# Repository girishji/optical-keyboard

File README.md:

Keyboard PCB for Gateron optical switches (KiCad project).

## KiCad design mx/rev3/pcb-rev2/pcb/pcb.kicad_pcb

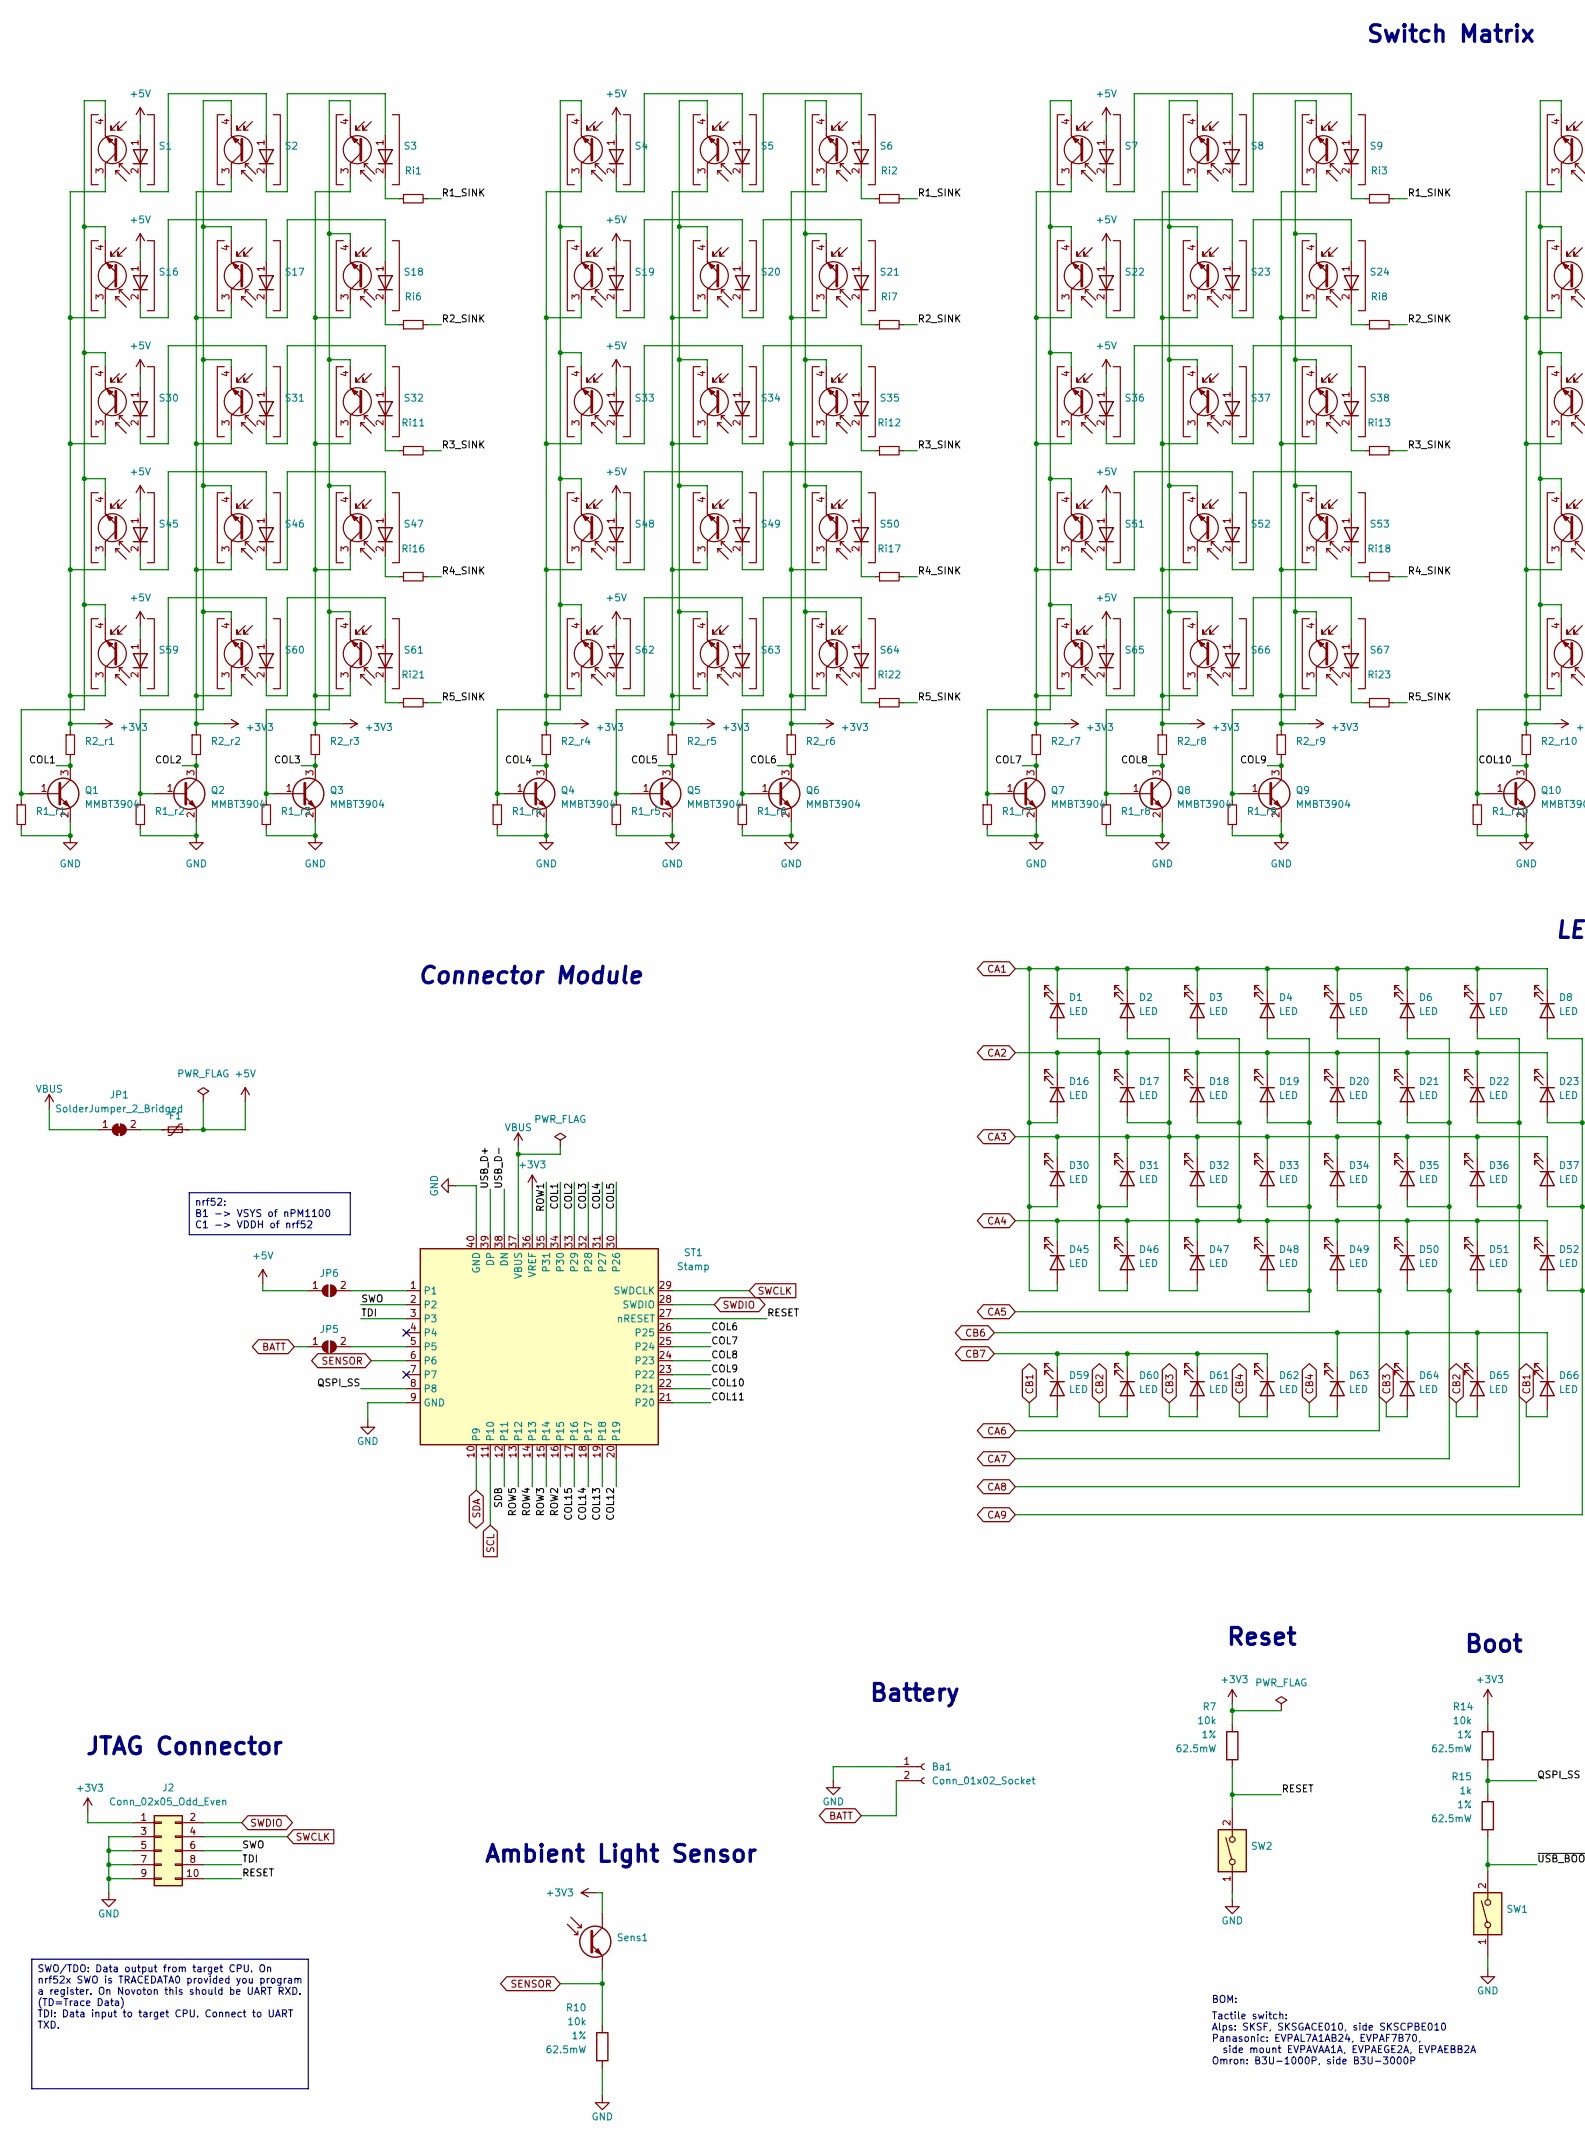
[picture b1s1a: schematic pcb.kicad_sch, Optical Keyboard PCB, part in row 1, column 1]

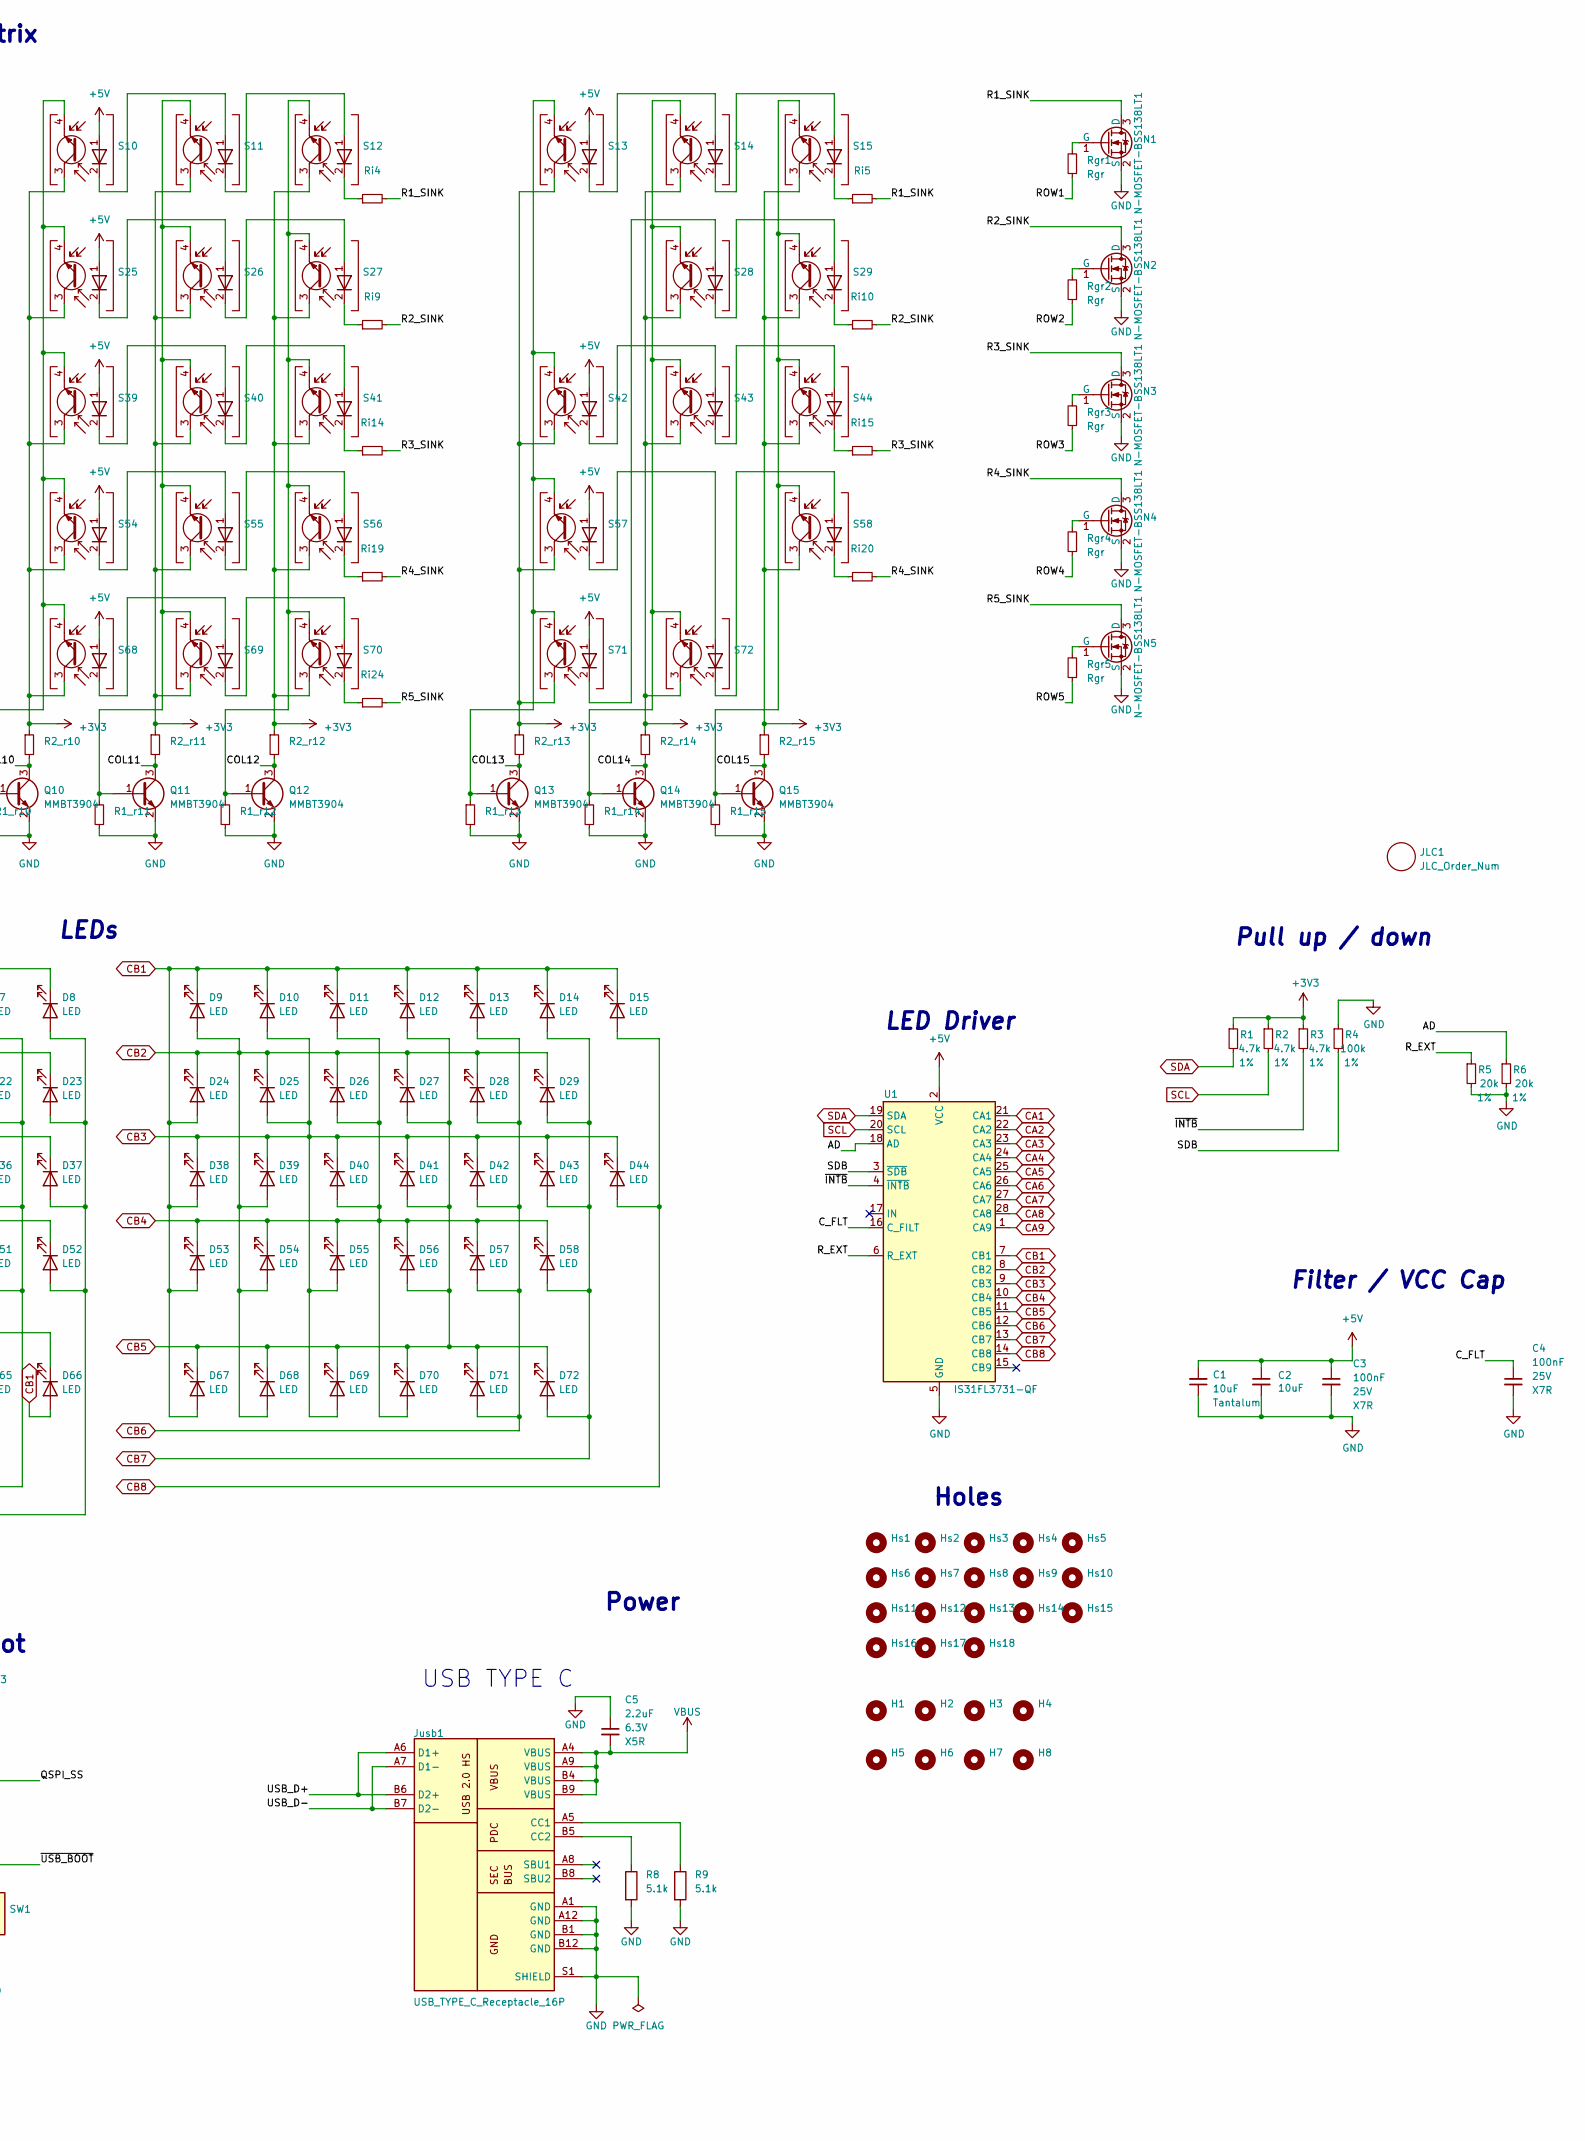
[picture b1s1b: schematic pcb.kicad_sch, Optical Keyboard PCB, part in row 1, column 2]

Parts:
Ba1: Conn_01x02_Socket; Battery_Pads_2x2.0x2.0mm
C1: 10uF; C_1206_3216Metric; JLC 10uF_tantalum
C2: 10uF; C_0603_1608Metric_Pad1.08x0.95mm_HandSolder; MPN CC0603MRX5R8BB106; LCSC C596327
C3, C4: 100nF; C_0603_1608Metric_Pad1.08x0.95mm_HandSolder; VOLTAGE RATING 25V; TOLERANCE TBD; MPN CL05B104KA5NNNC; LCSC C155422
C5: 2.2uF; C_0603_1608Metric_Pad1.08x0.95mm_HandSolder; VOLTAGE RATING 6.3V; TOLERANCE TBD; MPN CL05A225MQ5NNNC; LCSC C107371
D1, D2, D3, D4, D5, D6, D7, D8, D9, D10, D11, D12, D13, D14, D15, D16, D17, D18, D19, D20, D21, D22, D23, D24, D25, D26, D27, D28, D29, D30, D31, D32, D33, D34, D35, D36, D37, D38, D39, D40, D41, D42, D43, D44, D45, D46, D47, D48, D49, D50, D51, D52, D53, D54, D55, D56, D57, D58, D59, D60, D61, D62, D63, D64, D65, D66, D67, D68, D69, D70, D71, D72: LED; LED_0603_1608Metric
F1: 500ma; Fuse_0603_1608Metric; LCSC C210357
H1, H2, H3, H4, H5, H6, H7, H8: MountingHole; SMTSO_M2
Hs1, Hs2, Hs3, Hs4, Hs5, Hs6, Hs7, Hs8, Hs9, Hs10, Hs11, Hs12, Hs13, Hs14, Hs15, Hs16, Hs17, Hs18: SMTSO_M2
J2: Conn_02x05_Odd_Even; PinHeader_2x05_P1.27mm_Horizontal
JLC1: JLC_Order_Num
JP1: SolderJumper_2_Bridged; SolderJumper-2_P1.3mm_Bridged2Bar_RoundedPad1.0x1.5mm
JP5, JP6: SolderJumper_2_Open; SolderJumper-2_P1.3mm_Open_TrianglePad1.0x1.5mm
Jusb1: USB_TYPE_C_Receptacle_16P; USB_C_Receptacle_XKB_U262-16XN-4BVC11; MPN U262-161N-4BVC11; LCSC C319148
N1, N2, N3, N4, N5: N-MOSFET-BSS138LT1; SOT-23-3
Q1, Q2, Q3, Q4, Q5, Q6, Q7, Q8, Q9, Q10, Q11, Q12, Q13, Q14, Q15: MMBT3904; SOT-23
R1, R2, R3: 4.7k; R_0603_1608Metric_Pad0.98x0.95mm_HandSolder; Tolerance 1%; LCSC C105871
R1_r1, R1_r2, R1_r3, R1_r4, R1_r5, R1_r6, R1_r7, R1_r8, R1_r9, R1_r10, R1_r11, R1_r12, R1_r13, R1_r14, R1_r15: R1_r; R_0603_1608Metric; Power Rating 62.5mW; MPN RC0402FR-07160RL; LCSC C327369
R2_r1, R2_r2, R2_r3, R2_r4, R2_r5, R2_r6, R2_r7, R2_r8, R2_r9, R2_r10, R2_r11, R2_r12, R2_r13, R2_r14, R2_r15: R2_r; R_0603_1608Metric; Power Rating 62.5mW; MPN RC0402FR-07160RL; LCSC C327369
R4: 100k; R_0603_1608Metric_Pad0.98x0.95mm_HandSolder; Tolerance 1%; JLC 20k
R5, R6: 20k; R_0603_1608Metric_Pad0.98x0.95mm_HandSolder; Tolerance 1%; JLC 20k
R7, R10, R14: 10k; R_0603_1608Metric_Pad0.98x0.95mm_HandSolder; TOLERANCE 1%; POWER RATING 62.5mW; MPN RC0402FR-0710KL; LCSC C60490
R8, R9: 5.1k; R_0603_1608Metric_Pad0.98x0.95mm_HandSolder; TOLERANCE 1%; POWER RATING 62.5mW; MPN RC0402FR-075K1L; LCSC C105872
R15: 1k; R_0603_1608Metric_Pad0.98x0.95mm_HandSolder; TOLERANCE 1%; POWER RATING 62.5mW; MPN RC0402FR-071KL; LCSC C106235
Rgr1, Rgr2, Rgr3, Rgr4, Rgr5: Rgr; R_0603_1608Metric; Power Rating 62.5mW; MPN RC0402FR-07160RL; LCSC C327369
Ri1, Ri2, Ri3, Ri4, Ri5, Ri6, Ri7, Ri8, Ri9, Ri10, Ri11, Ri12, Ri13, Ri14, Ri15, Ri16, Ri17, Ri18, Ri19, Ri20, Ri21, Ri22, Ri23, Ri24: R_IR; R_0603_1608Metric
S1, S2, S3, S4, S5, S6, S7, S8, S9, S10, S11, S12, S13, S14, S15, S16, S17, S18, S19, S20, S21, S22, S23, S24, S25, S26, S27, S28, S29, S30, S31, S32, S33, S34, S35, S36, S37, S38, S39, S40, S41, S42, S43, S44, S45, S46, S47, S48, S49, S50, S51, S52, S53, S54, S55, S56, S57, S58, S59, S60, S61, S62, S65, S67, S68, S69, S70, S71, S72: OSw; Gateron_1u_v2
S63: OSw; Gateron_1.25u_v2
S64, S66: OSw; Gateron_2u_v2
ST1: Stamp; StampConnector
SW1, SW2: SW_DIP_x01_XKB_TS_2030; SW_B3U-3000P; MPN TS-2030-B; LCSC C2960614
Sens1: ALS-PT19; MPN 1N4148WT T4; LCSC C68948
U1: IS31FL3731-QF; QFN-28-1EP_4x4mm_P0.4mm_EP2.3x2.3mm; JLCPCB IS31FL3731-QFLS2-TR

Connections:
+3V3: J2.1, R1.1, R2.1, R2_r1.1, R2_r2.1, R2_r3.1, R2_r4.1, R2_r5.1, R2_r6.1, R2_r7.1, R2_r8.1, R2_r9.1, R2_r10.1, R2_r11.1, R2_r12.1, R2_r13.1, R2_r14.1, R2_r15.1, R3.1, R7.1, R14.1, S1.3 (C), S2.3 (C), S3.3 (C), S4.3 (C), S5.3 (C), S6.3 (C), S7.3 (C), S8.3 (C), S9.3 (C), S10.3 (C), S11.3 (C), S12.3 (C), S13.3 (C), S14.3 (C), S15.3 (C), S16.3 (C), S17.3 (C), S18.3 (C), S19.3 (C), S20.3 (C), S21.3 (C), S22.3 (C), S23.3 (C), S24.3 (C), S25.3 (C), S26.3 (C), S27.3 (C), S28.3 (C), S29.3 (C), S30.3 (C), S31.3 (C), S32.3 (C), S33.3 (C), S34.3 (C), S35.3 (C), S36.3 (C), S37.3 (C), S38.3 (C), S39.3 (C), S40.3 (C), S41.3 (C), S42.3 (C), S43.3 (C), S44.3 (C), S45.3 (C), S46.3 (C), S47.3 (C), S48.3 (C), S49.3 (C), S50.3 (C), S51.3 (C), S52.3 (C), S53.3 (C), S54.3 (C), S55.3 (C), S56.3 (C), S57.3 (C), S58.3 (C), S59.3 (C), S60.3 (C), S61.3 (C), S62.3 (C), S63.3 (C), S64.3 (C), S65.3 (C), S66.3 (C), S67.3 (C), S68.3 (C), S69.3 (C), S70.3 (C), S71.3 (C), S72.3 (C), ST1.36 (VREF), Sens1.1 (C)
+5V: C1.2, C2.1, C3.1, F1.2, JP6.1 (A), S1.1 (IR_A), S4.1 (IR_A), S7.1 (IR_A), S10.1 (IR_A), S13.1 (IR_A), S16.1 (IR_A), S19.1 (IR_A), S22.1 (IR_A), S25.1 (IR_A), S30.1 (IR_A), S33.1 (IR_A), S36.1 (IR_A), S39.1 (IR_A), S42.1 (IR_A), S45.1 (IR_A), S48.1 (IR_A), S51.1 (IR_A), S54.1 (IR_A), S57.1 (IR_A), S59.1 (IR_A), S62.1 (IR_A), S65.1 (IR_A), S68.1 (IR_A), S71.1 (IR_A), U1.2 (VCC)
/AD: R6.1, U1.18 (AD)
/COL1: Q1.3 (C), R2_r1.2, ST1.34 (P30)
/COL2: Q2.3 (C), R2_r2.2, ST1.33 (P29)
/COL3: Q3.3 (C), R2_r3.2, ST1.32 (P28)
/COL4: Q4.3 (C), R2_r4.2, ST1.31 (P27)
/COL5: Q5.3 (C), R2_r5.2, ST1.30 (P26)
/COL6: Q6.3 (C), R2_r6.2, ST1.26 (P25)
/COL7: Q7.3 (C), R2_r7.2, ST1.25 (P24)
/COL8: Q8.3 (C), R2_r8.2, ST1.24 (P23)
/COL9: Q9.3 (C), R2_r9.2, ST1.23 (P22)
/COL10: Q10.3 (C), R2_r10.2, ST1.22 (P21)
/COL11: Q11.3 (C), R2_r11.2, ST1.21 (P20)
/COL12: Q12.3 (C), R2_r12.2, ST1.20 (P19)
/COL13: Q13.3 (C), R2_r13.2, ST1.19 (P18)
/COL14: Q14.3 (C), R2_r14.2, ST1.18 (P17)
/COL15: Q15.3 (C), R2_r15.2, ST1.17 (P16)
/C_FLT: C4.1, U1.16 (C_FILT)
/QSPI_SS: R14.2, R15.1, ST1.8
/R1_SINK: N1.3 (D), Ri1.2, Ri2.2, Ri3.2, Ri4.2, Ri5.2
/R2_SINK: N2.3 (D), Ri6.2, Ri7.2, Ri8.2, Ri9.2, Ri10.2
/R3_SINK: N3.3 (D), Ri11.2, Ri12.2, Ri13.2, Ri14.2, Ri15.2
/R4_SINK: N4.3 (D), Ri16.2, Ri17.2, Ri18.2, Ri19.2, Ri20.2
/R5_SINK: N5.3 (D), Ri21.2, Ri22.2, Ri23.2, Ri24.2
/RESET: J2.10, R7.2, ST1.27 (nRESET), SW2.2
/ROW1: Rgr1.1, ST1.35 (P31)
/ROW2: Rgr2.1, ST1.16 (P15)
/ROW3: Rgr3.1, ST1.15 (P14)
/ROW4: Rgr4.1, ST1.14 (P13)
/ROW5: Rgr5.1, ST1.13 (P12)
/R_EXT: R5.1, U1.6 (R_EXT)
/SDB: R4.2, ST1.12 (P11), U1.3 (~SDB)
/SWO: J2.6, ST1.2
/TDI: J2.8, ST1.3
/USB_D+: Jusb1.A6 (D1+), Jusb1.B6 (D2+), ST1.39 (DP)
/USB_D-: Jusb1.A7 (D1-), Jusb1.B7 (D2-), ST1.38 (DN)
/~INTB: R3.2, U1.4 (~INTB)
/~USB_BOOT: R15.2, SW1.2
BATT: Ba1.2, JP5.1 (A)
CA1: D1.1 (K), D2.1 (K), D3.1 (K), D4.1 (K), D5.1 (K), D6.1 (K), D7.1 (K), D8.1 (K), D16.2 (A), D30.2 (A), D45.2 (A), U1.21 (CA1)
CA2: D1.2 (A), D16.1 (K), D17.1 (K), D18.1 (K), D19.1 (K), D20.1 (K), D21.1 (K), D22.1 (K), D23.1 (K), D31.2 (A), D46.2 (A), U1.22 (CA2)
CA3: D2.2 (A), D17.2 (A), D30.1 (K), D31.1 (K), D32.1 (K), D33.1 (K), D34.1 (K), D35.1 (K), D36.1 (K), D37.1 (K), D47.2 (A), U1.23 (CA3)
CA4: D3.2 (A), D18.2 (A), D32.2 (A), D45.1 (K), D46.1 (K), D47.1 (K), D48.1 (K), D49.1 (K), D50.1 (K), D51.1 (K), D52.1 (K), U1.24 (CA4)
CA5: D4.2 (A), D19.2 (A), D33.2 (A), D48.2 (A), U1.25 (CA5)
CA6: D5.2 (A), D20.2 (A), D34.2 (A), D49.2 (A), U1.26 (CA6)
CA7: D6.2 (A), D21.2 (A), D35.2 (A), D50.2 (A), U1.27 (CA7)
CA8: D7.2 (A), D22.2 (A), D36.2 (A), D51.2 (A), U1.28 (CA8)
CA9: D8.2 (A), D23.2 (A), D37.2 (A), D52.2 (A), U1.1 (CA9)
CB1: D9.1 (K), D10.1 (K), D11.1 (K), D12.1 (K), D13.1 (K), D14.1 (K), D15.1 (K), D24.2 (A), D38.2 (A), D53.2 (A), D59.2 (A), D66.2 (A), D67.2 (A), U1.7 (CB1)
CB2: D9.2 (A), D24.1 (K), D25.1 (K), D26.1 (K), D27.1 (K), D28.1 (K), D29.1 (K), D39.2 (A), D54.2 (A), D60.2 (A), D65.2 (A), D68.2 (A), U1.8 (CB2)
CB3: D10.2 (A), D25.2 (A), D38.1 (K), D39.1 (K), D40.1 (K), D41.1 (K), D42.1 (K), D43.1 (K), D44.1 (K), D55.2 (A), D61.2 (A), D64.2 (A), D69.2 (A), U1.9 (CB3)
CB4: D11.2 (A), D26.2 (A), D40.2 (A), D53.1 (K), D54.1 (K), D55.1 (K), D56.1 (K), D57.1 (K), D58.1 (K), D62.2 (A), D63.2 (A), D70.2 (A), U1.10 (CB4)
CB5: D12.2 (A), D27.2 (A), D41.2 (A), D56.2 (A), D67.1 (K), D68.1 (K), D69.1 (K), D70.1 (K), D71.1 (K), D72.1 (K), U1.11 (CB5)
CB6: D13.2 (A), D28.2 (A), D42.2 (A), D57.2 (A), D63.1 (K), D64.1 (K), D65.1 (K), D66.1 (K), D71.2 (A), U1.12 (CB6)
CB7: D14.2 (A), D29.2 (A), D43.2 (A), D58.2 (A), D59.1 (K), D60.1 (K), D61.1 (K), D62.1 (K), D72.2 (A), U1.13 (CB7)
CB8: D15.2 (A), D44.2 (A), U1.14 (CB8)
GND: Ba1.1, C1.1, C2.2, C3.2, C4.2, C5.1, J2.3, J2.5, J2.7, J2.9, Jusb1.A1 (GND), Jusb1.A12 (GND), Jusb1.B1 (GND), Jusb1.B12 (GND), Jusb1.S1 (SHIELD), N1.2 (S), N2.2 (S), N3.2 (S), N4.2 (S), N5.2 (S), Q1.2 (E), Q2.2 (E), Q3.2 (E), Q4.2 (E), Q5.2 (E), Q6.2 (E), Q7.2 (E), Q8.2 (E), Q9.2 (E), Q10.2 (E), Q11.2 (E), Q12.2 (E), Q13.2 (E), Q14.2 (E), Q15.2 (E), R1_r1.2, R1_r2.2, R1_r3.2, R1_r4.2, R1_r5.2, R1_r6.2, R1_r7.2, R1_r8.2, R1_r9.2, R1_r10.2, R1_r11.2, R1_r12.2, R1_r13.2, R1_r14.2, R1_r15.2, R4.1, R5.2, R6.2, R8.2, R9.2, R10.2, ST1.9 (GND), ST1.40 (GND), SW1.1, SW2.1, U1.5 (GND), U1.29 (GND)
unnamed: F1.1, JP1.2 (B)
unnamed: JP5.2 (B), ST1.5
unnamed: JP6.2 (B), ST1.1
unnamed: Jusb1.A5 (CC1), R9.1
unnamed: Jusb1.B5 (CC2), R8.1
unnamed: N1.1 (G), Rgr1.2
unnamed: N2.1 (G), Rgr2.2
unnamed: N3.1 (G), Rgr3.2
unnamed: N4.1 (G), Rgr4.2
unnamed: N5.1 (G), Rgr5.2
unnamed: Q1.1 (B), R1_r1.1, S1.4 (E), S16.4 (E), S30.4 (E), S45.4 (E), S59.4 (E)
unnamed: Q2.1 (B), R1_r2.1, S2.4 (E), S17.4 (E), S31.4 (E), S46.4 (E), S60.4 (E)
unnamed: Q3.1 (B), R1_r3.1, S3.4 (E), S18.4 (E), S32.4 (E), S47.4 (E), S61.4 (E)
unnamed: Q4.1 (B), R1_r4.1, S4.4 (E), S19.4 (E), S33.4 (E), S48.4 (E), S62.4 (E)
unnamed: Q5.1 (B), R1_r5.1, S5.4 (E), S20.4 (E), S34.4 (E), S49.4 (E), S63.4 (E)
unnamed: Q6.1 (B), R1_r6.1, S6.4 (E), S21.4 (E), S35.4 (E), S50.4 (E), S64.4 (E)
unnamed: Q7.1 (B), R1_r7.1, S7.4 (E), S22.4 (E), S36.4 (E), S51.4 (E), S65.4 (E)
unnamed: Q8.1 (B), R1_r8.1, S8.4 (E), S23.4 (E), S37.4 (E), S52.4 (E), S66.4 (E)
unnamed: Q9.1 (B), R1_r9.1, S9.4 (E), S24.4 (E), S38.4 (E), S53.4 (E), S67.4 (E)
unnamed: Q10.1 (B), R1_r10.1, S10.4 (E), S25.4 (E), S39.4 (E), S54.4 (E), S68.4 (E)
unnamed: Q11.1 (B), R1_r11.1, S11.4 (E), S26.4 (E), S40.4 (E), S55.4 (E), S69.4 (E)
unnamed: Q12.1 (B), R1_r12.1, S12.4 (E), S27.4 (E), S41.4 (E), S56.4 (E), S70.4 (E)
unnamed: Q13.1 (B), R1_r13.1, S13.4 (E), S42.4 (E), S57.4 (E), S71.4 (E)
unnamed: Q14.1 (B), R1_r14.1, S14.4 (E), S28.4 (E), S43.4 (E), S72.4 (E)
unnamed: Q15.1 (B), R1_r15.1, S15.4 (E), S29.4 (E), S44.4 (E), S58.4 (E)
unnamed: S1.2 (IR_K), S2.1 (IR_A)
unnamed: S2.2 (IR_K), S3.1 (IR_A)
unnamed: Ri1.1, S3.2 (IR_K)
unnamed: S4.2 (IR_K), S5.1 (IR_A)
unnamed: S5.2 (IR_K), S6.1 (IR_A)
unnamed: Ri2.1, S6.2 (IR_K)
unnamed: S7.2 (IR_K), S8.1 (IR_A)
unnamed: S8.2 (IR_K), S9.1 (IR_A)
unnamed: Ri3.1, S9.2 (IR_K)
unnamed: S10.2 (IR_K), S11.1 (IR_A)
unnamed: S11.2 (IR_K), S12.1 (IR_A)
unnamed: Ri4.1, S12.2 (IR_K)
unnamed: S13.2 (IR_K), S14.1 (IR_A)
unnamed: S14.2 (IR_K), S15.1 (IR_A)
unnamed: Ri5.1, S15.2 (IR_K)
unnamed: S16.2 (IR_K), S17.1 (IR_A)
unnamed: S17.2 (IR_K), S18.1 (IR_A)
unnamed: Ri6.1, S18.2 (IR_K)
unnamed: S19.2 (IR_K), S20.1 (IR_A)
unnamed: S20.2 (IR_K), S21.1 (IR_A)
unnamed: Ri7.1, S21.2 (IR_K)
unnamed: S22.2 (IR_K), S23.1 (IR_A)
unnamed: S23.2 (IR_K), S24.1 (IR_A)
unnamed: Ri8.1, S24.2 (IR_K)
unnamed: S25.2 (IR_K), S26.1 (IR_A)
unnamed: S26.2 (IR_K), S27.1 (IR_A)
unnamed: Ri9.1, S27.2 (IR_K)
unnamed: S28.1 (IR_A), S71.2 (IR_K)
unnamed: S28.2 (IR_K), S29.1 (IR_A)
unnamed: Ri10.1, S29.2 (IR_K)
unnamed: S30.2 (IR_K), S31.1 (IR_A)
unnamed: S31.2 (IR_K), S32.1 (IR_A)
unnamed: Ri11.1, S32.2 (IR_K)
unnamed: S33.2 (IR_K), S34.1 (IR_A)
unnamed: S34.2 (IR_K), S35.1 (IR_A)
unnamed: Ri12.1, S35.2 (IR_K)
unnamed: S36.2 (IR_K), S37.1 (IR_A)
unnamed: S37.2 (IR_K), S38.1 (IR_A)
unnamed: Ri13.1, S38.2 (IR_K)
unnamed: S39.2 (IR_K), S40.1 (IR_A)
unnamed: S40.2 (IR_K), S41.1 (IR_A)
unnamed: Ri14.1, S41.2 (IR_K)
unnamed: S42.2 (IR_K), S43.1 (IR_A)
unnamed: S43.2 (IR_K), S44.1 (IR_A)
unnamed: Ri15.1, S44.2 (IR_K)
unnamed: S45.2 (IR_K), S46.1 (IR_A)
unnamed: S46.2 (IR_K), S47.1 (IR_A)
unnamed: Ri16.1, S47.2 (IR_K)
unnamed: S48.2 (IR_K), S49.1 (IR_A)
unnamed: S49.2 (IR_K), S50.1 (IR_A)
unnamed: Ri17.1, S50.2 (IR_K)
unnamed: S51.2 (IR_K), S52.1 (IR_A)
unnamed: S52.2 (IR_K), S53.1 (IR_A)
unnamed: Ri18.1, S53.2 (IR_K)
unnamed: S54.2 (IR_K), S55.1 (IR_A)
unnamed: S55.2 (IR_K), S56.1 (IR_A)
unnamed: Ri19.1, S56.2 (IR_K)
unnamed: S57.2 (IR_K), S72.1 (IR_A)
unnamed: S58.1 (IR_A), S72.2 (IR_K)
unnamed: Ri20.1, S58.2 (IR_K)
unnamed: S59.2 (IR_K), S60.1 (IR_A)
unnamed: S60.2 (IR_K), S61.1 (IR_A)
unnamed: Ri21.1, S61.2 (IR_K)
unnamed: S62.2 (IR_K), S63.1 (IR_A)
unnamed: S63.2 (IR_K), S64.1 (IR_A)
unnamed: Ri22.1, S64.2 (IR_K)
unnamed: S65.2 (IR_K), S66.1 (IR_A)
unnamed: S66.2 (IR_K), S67.1 (IR_A)
unnamed: Ri23.1, S67.2 (IR_K)
unnamed: S68.2 (IR_K), S69.1 (IR_A)
unnamed: S69.2 (IR_K), S70.1 (IR_A)
unnamed: Ri24.1, S70.2 (IR_K)
SCL: R2.2, ST1.11 (P10), U1.20 (SCL)
SDA: R1.2, ST1.10 (P9), U1.19 (SDA)
SENSOR: R10.1, ST1.6, Sens1.2 (E)
SWCLK: J2.4, ST1.29 (SWDCLK)
SWDIO: J2.2, ST1.28 (SWDIO)
VBUS: C5.2, JP1.1 (A), Jusb1.A4 (VBUS), Jusb1.A9 (VBUS), Jusb1.B4 (VBUS), Jusb1.B9 (VBUS), ST1.37 (VBUS)

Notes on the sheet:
Pull up / down
Holes
Power
JTAG Connector
USB TYPE C
Reset
LEDs
Connector Module
Switch Matrix
Battery
BOM:
Ambient Light Sensor
Tactile switch: Alps: SKSF, SKSGACE010, side SKSCPBE010 Panasonic: EVPAL7A1AB24, EVPAF7B70, side mount EVPAVAA1A, EVPAEGE2A, EVPAEBB2A Omron: B3U-1000P, side B3U-3000P
Filter / VCC Cap
LED Driver
Boot
SWO/TDO: Data output from target CPU. On nrf52x SWO is TRACEDATA0 provided you program a register. On Novoton this should be UART RXD. (TD=Trace Data) TDI: Data input to target CPU. Connect to UART TXD.
nrf52: B1 -> VSYS of nPM1100 C1 -> VDDH of nrf52

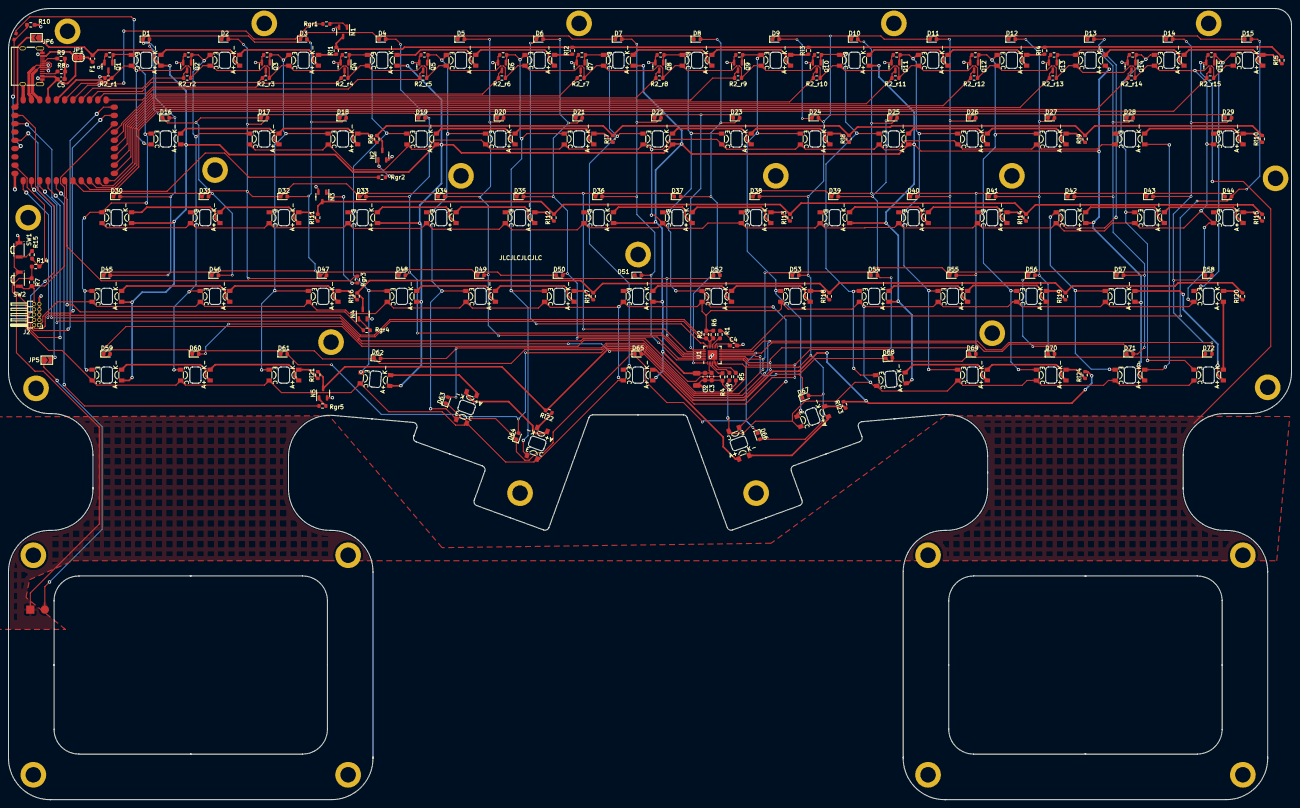
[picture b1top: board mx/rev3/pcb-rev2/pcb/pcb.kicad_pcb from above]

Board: 2 copper layers, 309.8 x 191.0 mm, 279 parts (0 on the bottom side), 161 nets.

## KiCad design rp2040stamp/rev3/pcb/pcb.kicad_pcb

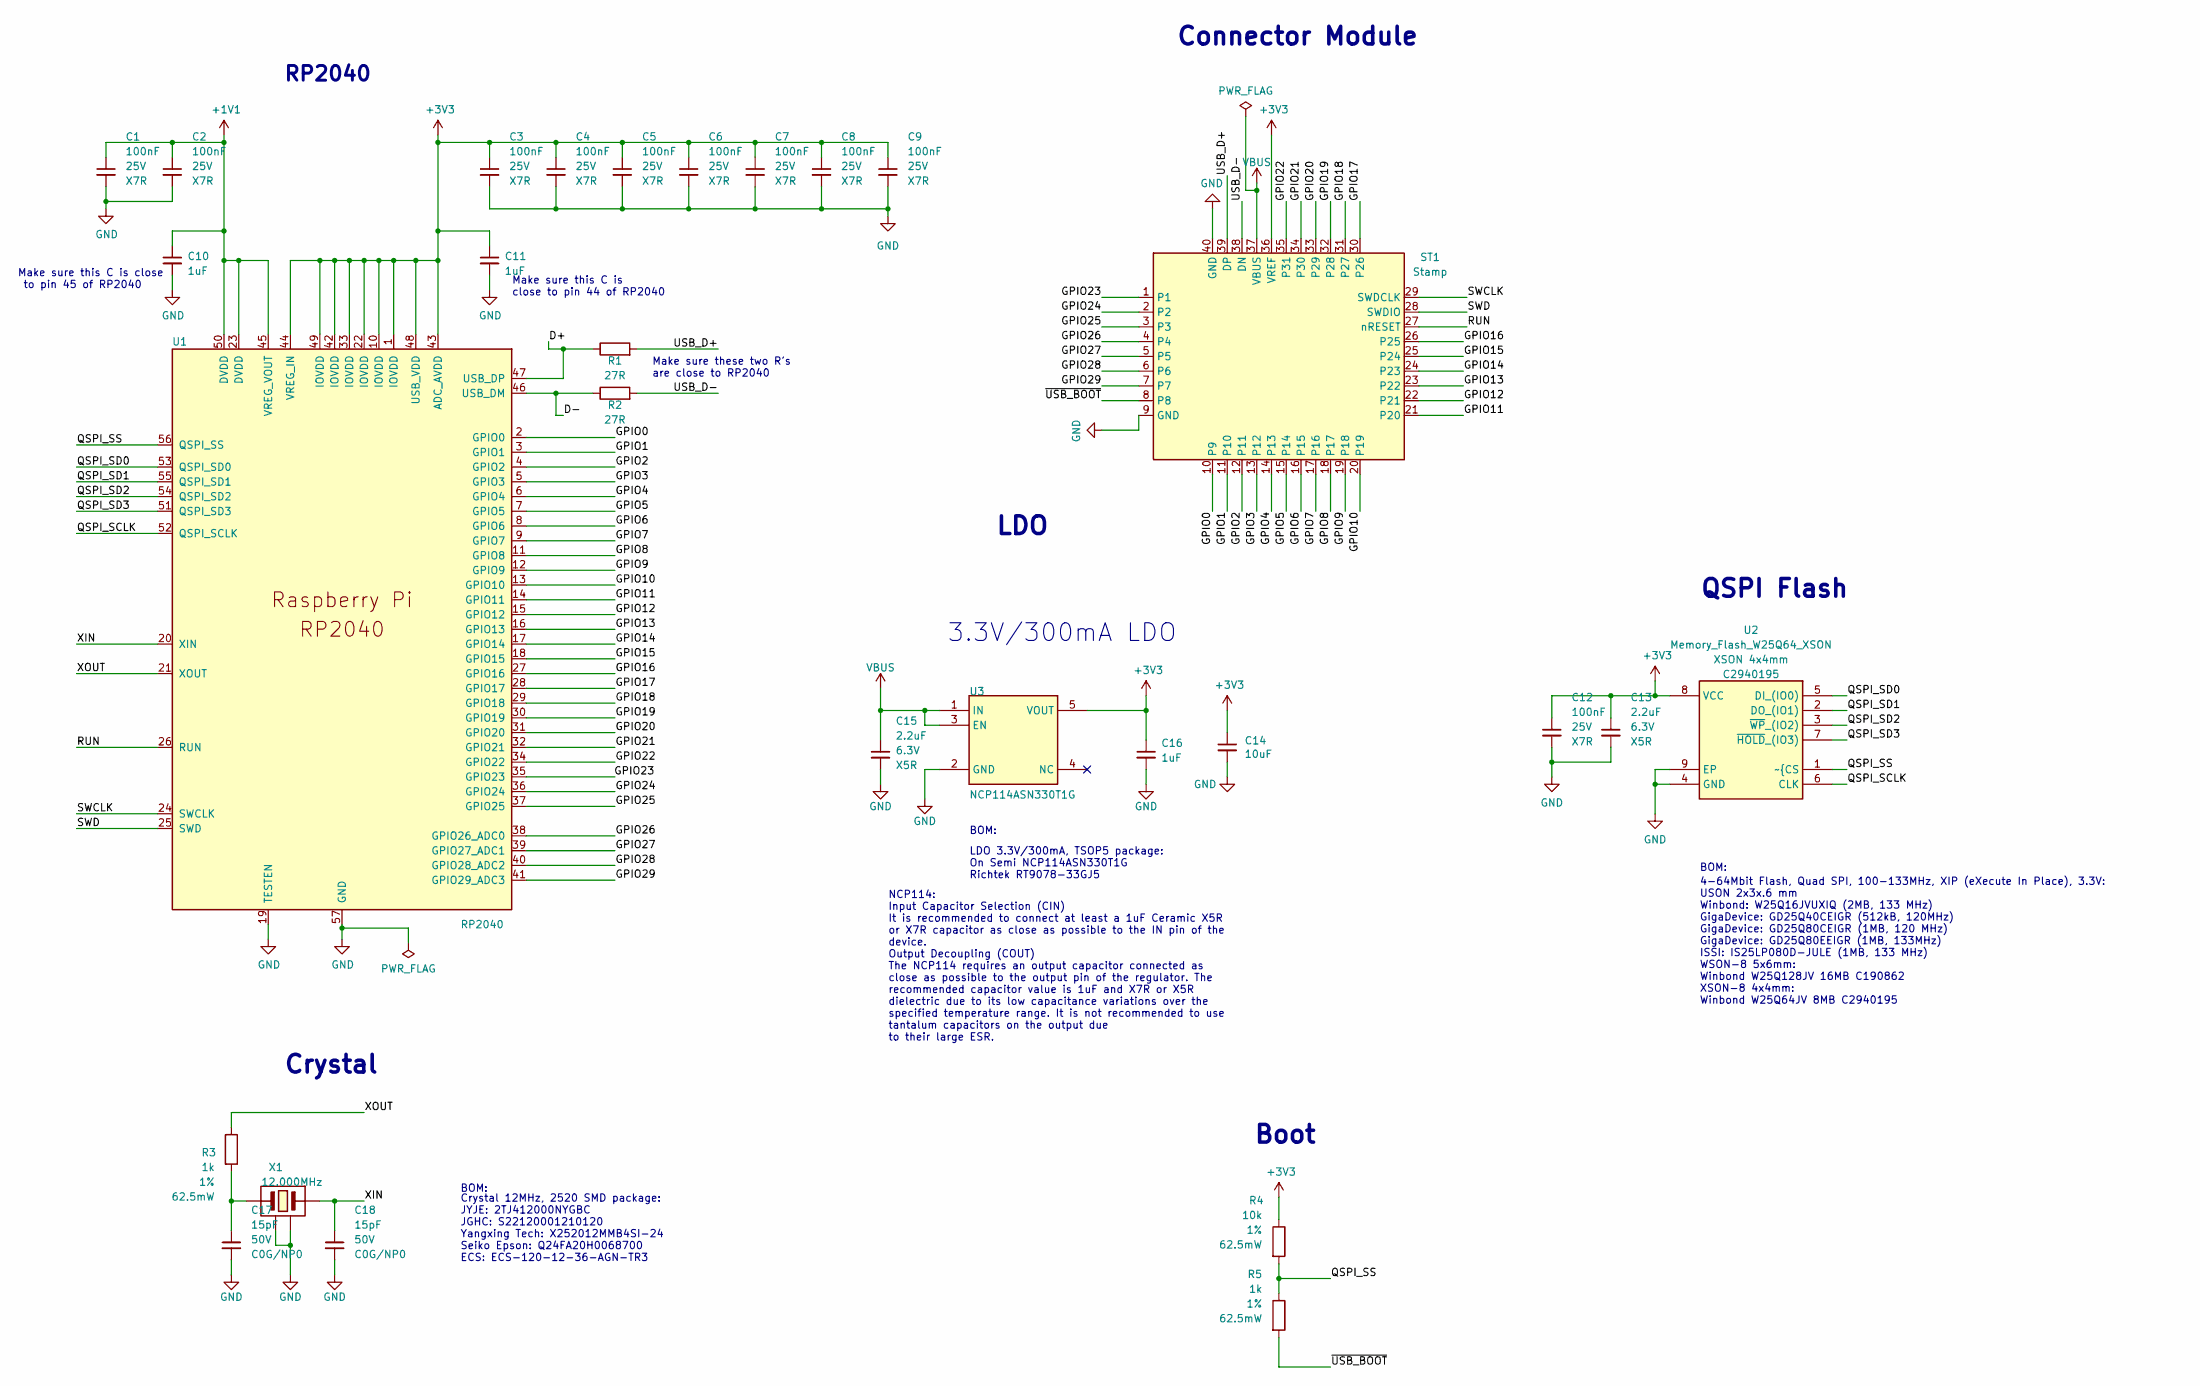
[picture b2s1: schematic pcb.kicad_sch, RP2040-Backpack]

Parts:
C1, C2, C3, C4, C5, C6, C7, C8, C9, C12: 100nF; C_0603_1608Metric; VOLTAGE RATING 25V; TOLERANCE TBD; MPN CL05B104KA5NNNC; LCSC C155422
C10, C11, C16: 1uF; C_0603_1608Metric; MPN CC0402KRX5R6BB105; LCSC C106254
C13, C15: 2.2uF; C_0603_1608Metric; VOLTAGE RATING 6.3V; TOLERANCE TBD; MPN CL05A225MQ5NNNC; LCSC C107371
C14: 10uF; C_0603_1608Metric; MPN CC0603MRX5R8BB106; LCSC C596327
C17, C18: 15pF; C_0603_1608Metric; VOLTAGE RATING 50V; TOLERANCE TBD; MPN C0402C150J5GACTU; LCSC C106997
R1, R2: 27R; R_0603_1608Metric; TOLERANCE 1%; POWER RATING 62.5mW; MPN RC0402FR-0727RL; LCSC C138021
R3: 1k; R_0603_1608Metric; TOLERANCE 1%; POWER RATING 62.5mW; MPN RC0402FR-071KL; LCSC C106235
R4: 10k; R_0603_1608Metric_Pad0.98x0.95mm_HandSolder; TOLERANCE 1%; POWER RATING 62.5mW; MPN RC0402FR-0710KL; LCSC C60490
R5: 1k; R_0603_1608Metric_Pad0.98x0.95mm_HandSolder; TOLERANCE 1%; POWER RATING 62.5mW; MPN RC0402FR-071KL; LCSC C106235
ST1: Stamp
U1: RP2040; RP2040-QFN-56; LCSC C2040
U2: Memory_Flash_W25Q64_XSON; 8-USON-Handsolder; MPN W25Q64JV; LCSC C2940195
U3: NCP114ASN330T1G; TSOP-5_1.65x3.05mm_P0.95mm; MPN NCP114ASN330T1G; LCSC C457666
X1: 12.000MHz; Crystal_SMD_2520-4Pin_2.5x2.0mm-Handsolder; MPN Q24FA20H0068700; LCSC C90603

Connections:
+1V1: C1.1, C2.1, C10.1, U1.23 (DVDD), U1.45 (VREG_VOUT), U1.50 (DVDD)
+3V3: C3.1, C4.1, C5.1, C6.1, C7.1, C8.1, C9.1, C11.1, C12.1, C13.1, C14.1, C16.1, R4.1, ST1.36 (VREF), U1.1 (IOVDD), U1.10 (IOVDD), U1.22 (IOVDD), U1.33 (IOVDD), U1.42 (IOVDD), U1.43 (ADC_AVDD), U1.44 (VREG_IN), U1.48 (USB_VDD), U1.49 (IOVDD), U2.8 (VCC), U3.5 (VOUT)
/D+: R1.1, U1.47 (USB_DP)
/D-: R2.1, U1.46 (USB_DM)
/GPIO0: ST1.10 (P9), U1.2 (GPIO0)
/GPIO1: ST1.11 (P10), U1.3 (GPIO1)
/GPIO2: ST1.12 (P11), U1.4 (GPIO2)
/GPIO3: ST1.13 (P12), U1.5 (GPIO3)
/GPIO4: ST1.14 (P13), U1.6 (GPIO4)
/GPIO5: ST1.15 (P14), U1.7 (GPIO5)
/GPIO6: ST1.16 (P15), U1.8 (GPIO6)
/GPIO7: ST1.17 (P16), U1.9 (GPIO7)
/GPIO8: ST1.18 (P17), U1.11 (GPIO8)
/GPIO9: ST1.19 (P18), U1.12 (GPIO9)
/GPIO10: ST1.20 (P19), U1.13 (GPIO10)
/GPIO11: ST1.21 (P20), U1.14 (GPIO11)
/GPIO12: ST1.22 (P21), U1.15 (GPIO12)
/GPIO13: ST1.23 (P22), U1.16 (GPIO13)
/GPIO14: ST1.24 (P23), U1.17 (GPIO14)
/GPIO15: ST1.25 (P24), U1.18 (GPIO15)
/GPIO16: ST1.26 (P25), U1.27 (GPIO16)
/GPIO17: ST1.30 (P26), U1.28 (GPIO17)
/GPIO18: ST1.31 (P27), U1.29 (GPIO18)
/GPIO19: ST1.32 (P28), U1.30 (GPIO19)
/GPIO20: ST1.33 (P29), U1.31 (GPIO20)
/GPIO21: ST1.34 (P30), U1.32 (GPIO21)
/GPIO22: ST1.35 (P31), U1.34 (GPIO22)
/GPIO23: ST1.1, U1.35 (GPIO23)
/GPIO24: ST1.2, U1.36 (GPIO24)
/GPIO25: ST1.3, U1.37 (GPIO25)
/GPIO26: ST1.4, U1.38 (GPIO26_ADC0)
/GPIO27: ST1.5, U1.39 (GPIO27_ADC1)
/GPIO28: ST1.6, U1.40 (GPIO28_ADC2)
/GPIO29: ST1.7, U1.41 (GPIO29_ADC3)
/QSPI_SCLK: U1.52 (QSPI_SCLK), U2.6 (CLK)
/QSPI_SD0: U1.53 (QSPI_SD0), U2.5 (DI_(IO0))
/QSPI_SD1: U1.55 (QSPI_SD1), U2.2 (DO_(IO1))
/QSPI_SD2: U1.54 (QSPI_SD2), U2.3 (~WP_(IO2))
/QSPI_SD3: U1.51 (QSPI_SD3), U2.7 (~HOLD_(IO3))
/QSPI_SS: R4.2, R5.1, U1.56 (QSPI_SS), U2.1 (~{CS)
/RUN: ST1.27 (nRESET), U1.26 (RUN)
/SWCLK: ST1.29 (SWDCLK), U1.24 (SWCLK)
/SWD: ST1.28 (SWDIO), U1.25 (SWD)
/USB_D+: R1.2, ST1.39 (DP)
/USB_D-: R2.2, ST1.38 (DN)
/XIN: C18.1, U1.20 (XIN), X1.3
/XOUT: R3.1, U1.21 (XOUT)
/~USB_BOOT: R5.2, ST1.8
GND: C1.2, C2.2, C3.2, C4.2, C5.2, C6.2, C7.2, C8.2, C9.2, C10.2, C11.2, C12.2, C13.2, C14.2, C15.2, C16.2, C17.2, C18.2, ST1.9 (GND), ST1.40 (GND), U1.19 (TESTEN), U1.57 (GND), U2.4 (GND), U2.9 (EP), U3.2 (GND), X1.2, X1.4
unnamed: C17.1, R3.2, X1.1
VBUS: C15.1, ST1.37 (VBUS), U3.1 (IN), U3.3 (EN)

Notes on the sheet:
NCP114: Input Capacitor Selection (CIN) It is recommended to connect at least a 1uF Ceramic X5R or X7R capacitor as close as possible to the IN pin of the device. Output Decoupling (COUT) The NCP114 requires an output capacitor connected as close as possible to the output pin of the regulator. The 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
BOM:
LDO
LDO 3.3V/300mA, TSOP5 package: On Semi NCP114ASN330T1G Richtek RT9078-33GJ5
Crystal
Make sure these two R's are close to RP2040
Make sure this C is close to pin 45 of RP2040
Connector Module
4-64Mbit Flash, Quad SPI, 100-133MHz, XIP (eXecute In Place), 3.3V: USON 2x3x.6 mm Winbond: W25Q16JVUXIQ (2MB, 133 MHz) GigaDevice: GD25Q40CEIGR (512kB, 120MHz) GigaDevice: GD25Q80CEIGR (1MB, 120 MHz) GigaDevice: GD25Q80EEIGR (1MB, 133MHz) ISSI: IS25LP080D-JULE (1MB, 133 MHz) WSON-8 5x6mm: Winbond 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
Make sure this C is close to pin 44 of RP2040
3.3V/300mA LDO
QSPI Flash
Boot
Crystal 12MHz, 2520 SMD package: JYJE: 2TJ412000NYGBC JGHC: S22120001210120 Yangxing Tech: X252012MMB4SI-24 Seiko Epson: Q24FA20H0068700 ECS: ECS-120-12-36-AGN-TR3
RP2040

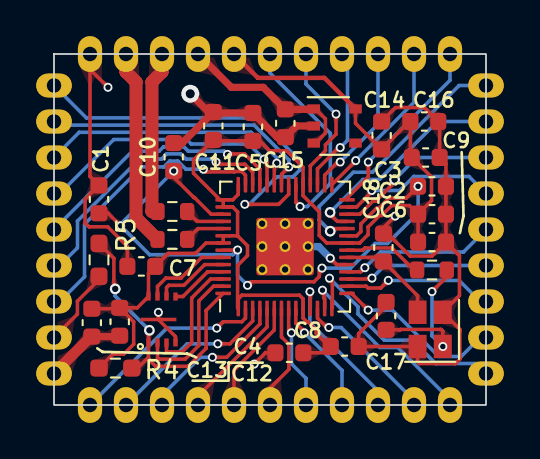
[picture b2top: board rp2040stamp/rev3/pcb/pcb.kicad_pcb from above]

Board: 2 copper layers, 24.0 x 19.5 mm, 28 parts (0 on the bottom side), 51 nets.
